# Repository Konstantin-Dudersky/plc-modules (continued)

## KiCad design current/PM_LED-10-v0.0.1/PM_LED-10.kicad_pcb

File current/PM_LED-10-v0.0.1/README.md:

## v0.0.1

- Сделано на основе платы с 8 светодиодами

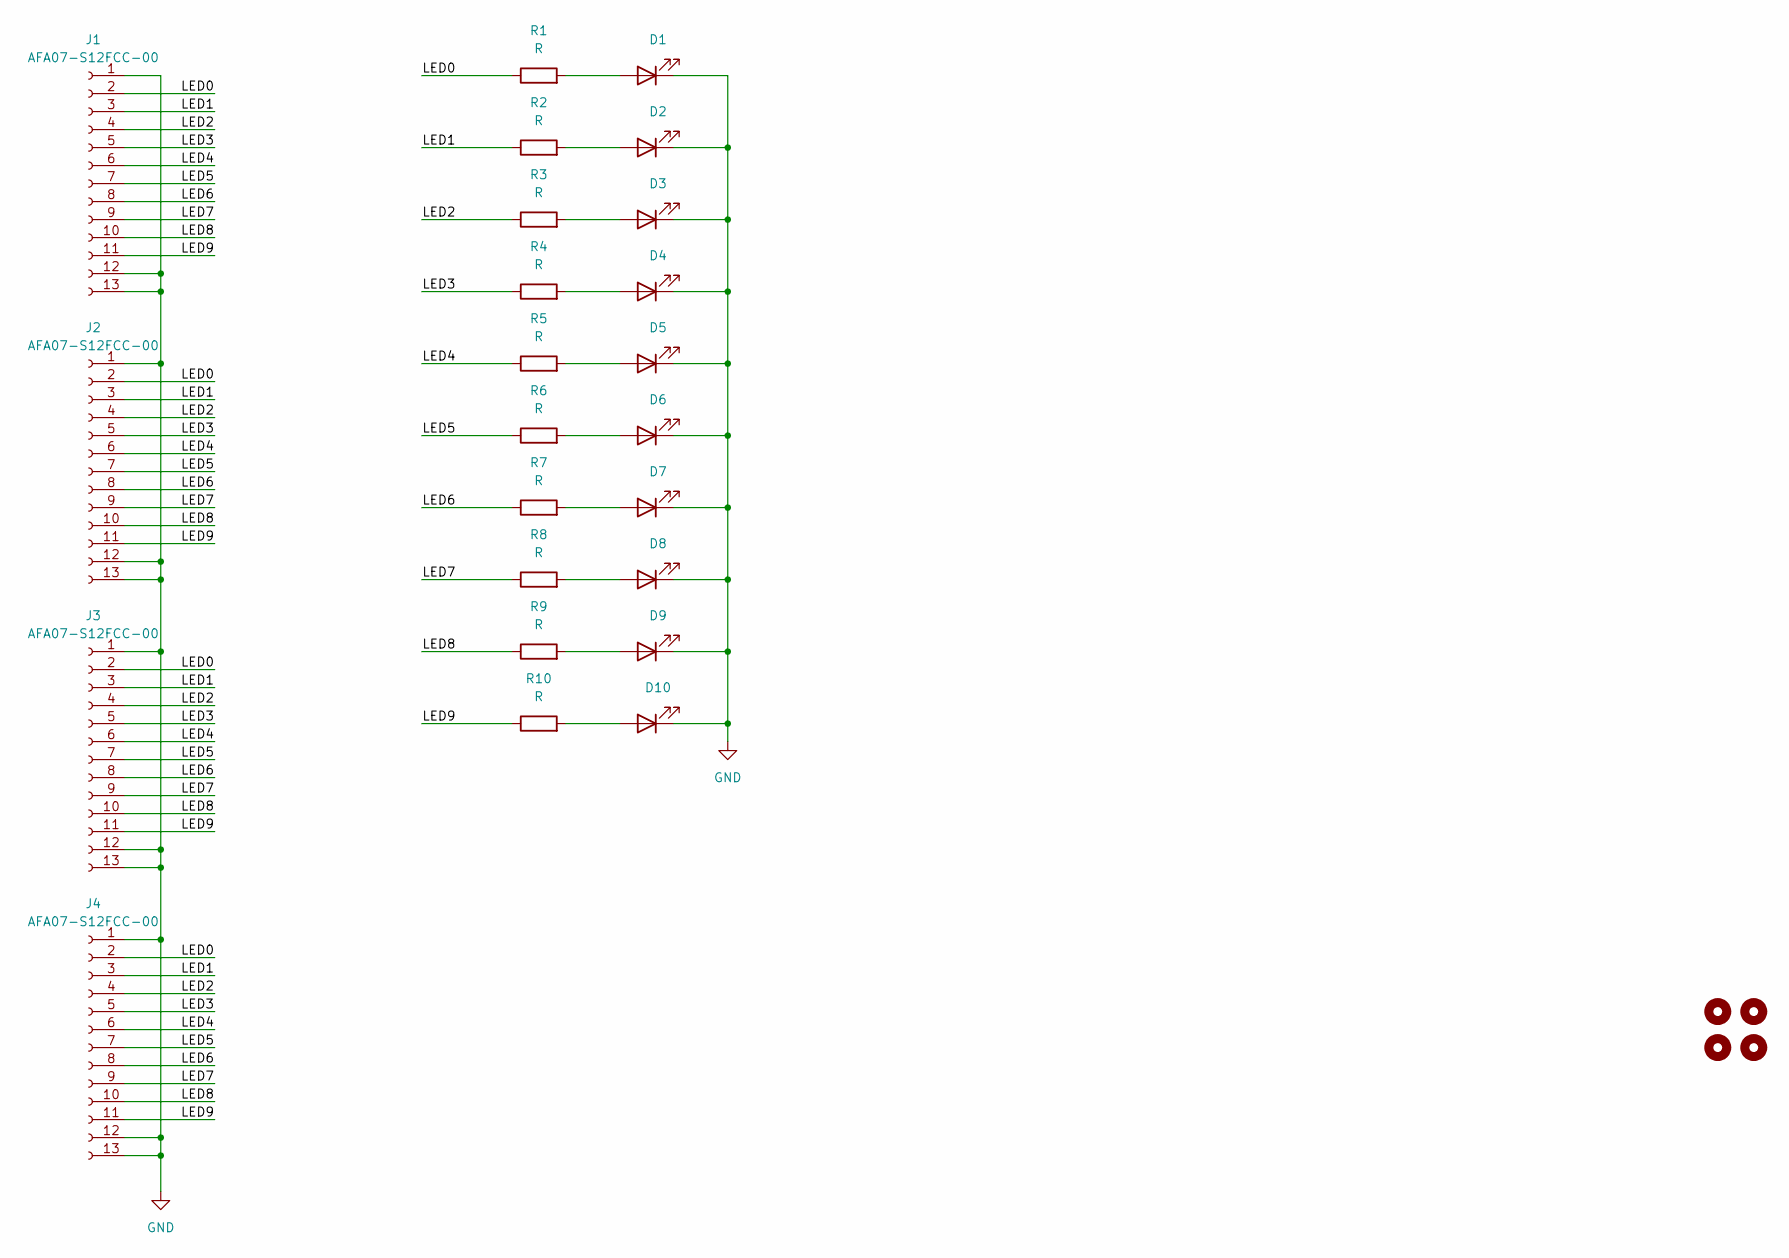
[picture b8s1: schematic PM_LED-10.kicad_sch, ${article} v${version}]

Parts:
D1, D2, D3, D4, D5, D6, D7, D8, D9, D10: XL-1606SYGC; XL-1606; part_ipn XL-1606SYGC
H1, H2, H3, H4: MountingHole_M2
J1, J2, J3, J4: AFA07-S12FCC-00; CONN10_AFA07-S12_JUS; part_ipn AFA07-S12FCC-00
R1, R2, R3, R4, R5, R6, R7, R8, R9, R10: R; R_0603_1608Metric

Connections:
/LED0: J1.2, J2.2, J3.2, J4.2, R1.1
/LED1: J1.3, J2.3, J3.3, J4.3, R2.1
/LED2: J1.4, J2.4, J3.4, J4.4, R3.1
/LED3: J1.5, J2.5, J3.5, J4.5, R4.1
/LED4: J1.6, J2.6, J3.6, J4.6, R5.1
/LED5: J1.7, J2.7, J3.7, J4.7, R6.1
/LED6: J1.8, J2.8, J3.8, J4.8, R7.1
/LED7: J1.9, J2.9, J3.9, J4.9, R8.1
/LED8: J1.10, J2.10, J3.10, J4.10, R9.1
/LED9: J1.11, J2.11, J3.11, J4.11, R10.1
GND: D1.1 (K), D2.1 (K), D3.1 (K), D4.1 (K), D5.1 (K), D6.1 (K), D7.1 (K), D8.1 (K), D9.1 (K), D10.1 (K), J1.1, J1.12 (Pin_11), J1.13 (Pin_11), J2.1, J2.12 (Pin_11), J2.13 (Pin_11), J3.1, J3.12 (Pin_11), J3.13 (Pin_11), J4.1, J4.12 (Pin_11), J4.13 (Pin_11)
unnamed: D1.2 (A), R1.2
unnamed: D2.2 (A), R2.2
unnamed: D3.2 (A), R3.2
unnamed: D4.2 (A), R4.2
unnamed: D5.2 (A), R5.2
unnamed: D6.2 (A), R6.2
unnamed: D7.2 (A), R7.2
unnamed: D8.2 (A), R8.2
unnamed: D9.2 (A), R9.2
unnamed: D10.2 (A), R10.2

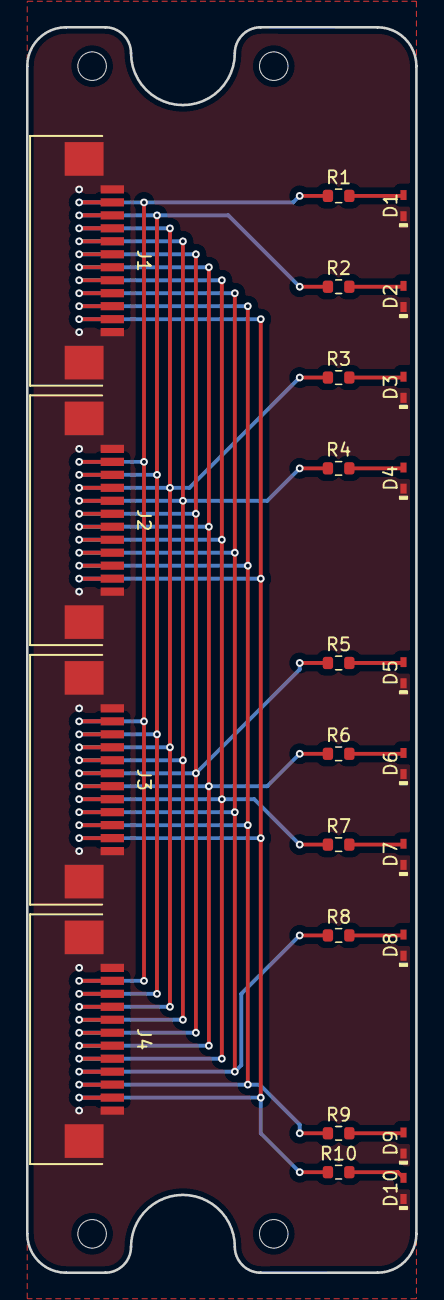
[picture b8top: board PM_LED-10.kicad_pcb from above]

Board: 2 copper layers, 30.0 x 96.0 mm, 29 parts (1 on the bottom side), 21 nets.

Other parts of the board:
Logo_kicad: KiCad-Logo2_5mm_SilkScreen
